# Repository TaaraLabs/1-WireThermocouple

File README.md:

1-Wire Thermocouple
==============

[WebSite](https://taaralabs.eu/tc1)

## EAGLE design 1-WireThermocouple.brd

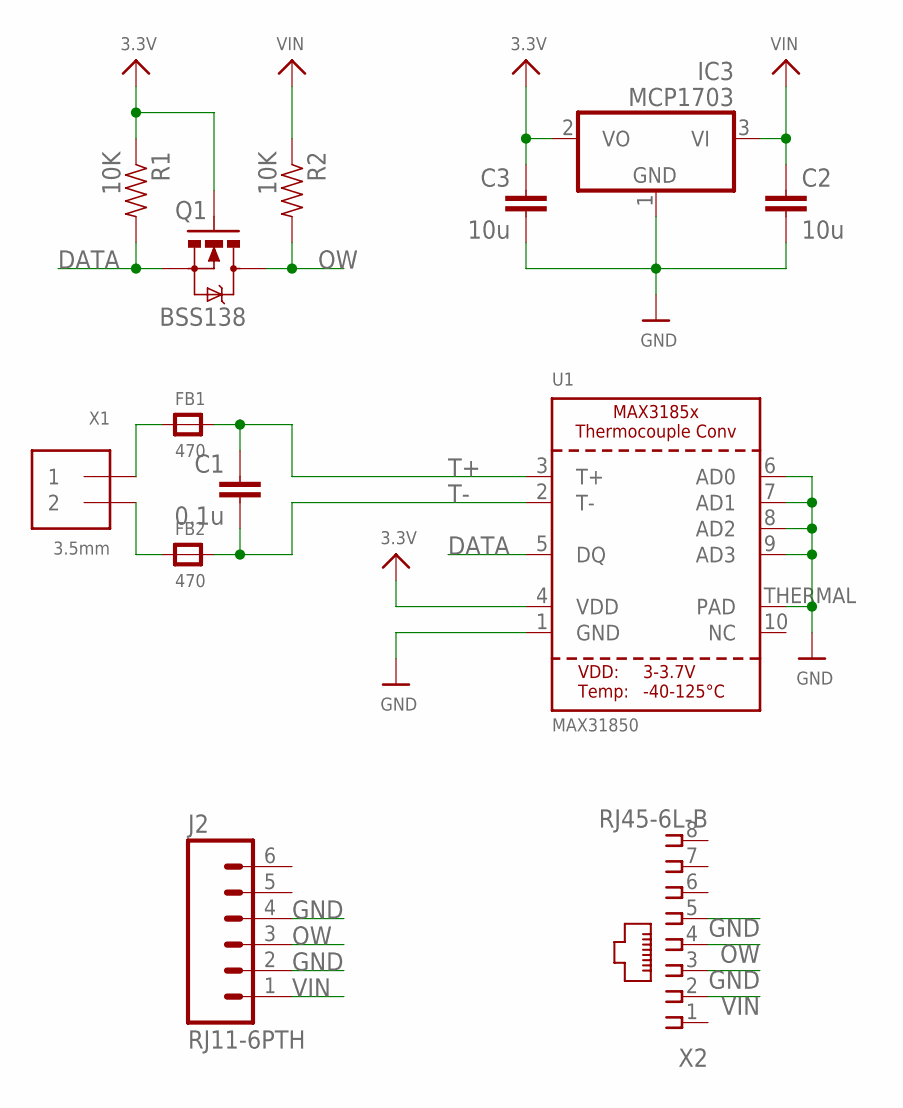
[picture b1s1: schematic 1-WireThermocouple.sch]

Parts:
C1: 0.1u; 0603-CAP
C2, C3: 10u; 0603-CAP
FB1, FB2: 470; 0603
IC3: MCP1703; SOT23
J2: RJ11-6PTH; RJ11-6
Q1: BSS138; SOT23-3
R1, R2: 10K; 0603-RES
U1: MAX31850; TDFN10_3X4MM
X1: 3.5mm; TERMBLOCK_1X2-3.5MM
X2: RJ45-6L-B; RJ45-NO-SHIELD

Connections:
3.3V: C3.1, IC3.2 (VO), Q1.1 (G), R1.1, U1.4 (VDD)
DATA: Q1.2 (S), R1.2, U1.5 (DQ)
GND: C2.2, C3.2, IC3.1 (GND), J2.2, J2.4, U1.1 (GND), U1.6 (AD0), U1.7 (AD1), U1.8 (AD2), U1.9 (AD3), U1.THERMAL (PAD), X2.3, X2.5
unnamed: FB1.1, X1.1
unnamed: FB2.1, X1.2
OW: J2.3, Q1.3 (D), R2.2, X2.4
T+: C1.1, FB1.2, U1.3 (T+)
T-: C1.2, FB2.2, U1.2 (T-)
VIN: C2.1, IC3.3 (VI), J2.1, R2.1, X2.2

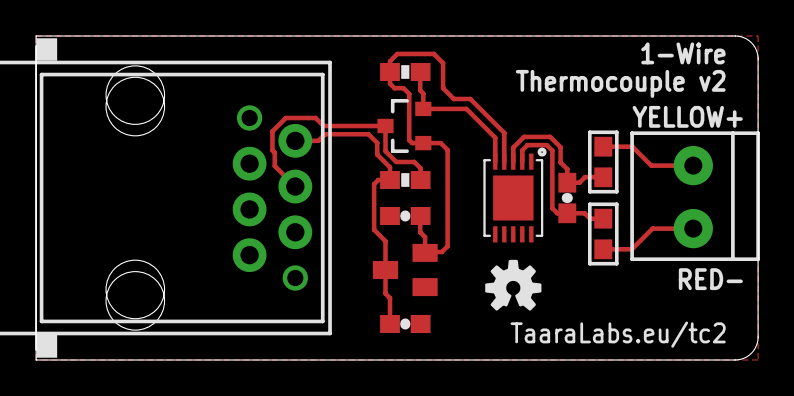
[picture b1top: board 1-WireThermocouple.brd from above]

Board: 2 copper layers, 40.1 x 18.0 mm, 15 parts (1 on the bottom side), 9 nets.

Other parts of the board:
U$1: OSHW-LOGO-S
U$8: OSHW-LOGO-L

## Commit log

2015-01-22 :octocat: Added .gitattributes & .gitignore files
2015-01-22 1-Wire Thermocouple
2019-04-16 LDO footprint fixed
2019-04-16 new images

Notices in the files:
parts and their libraries:
microbuilder: This work is placed in the public domain, and may be freely used for commercial and non-commercial work with the following conditions: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
SparkFun: Licensing: CC v3.0 Share-Alike You are welcome to use this library for commercial purposes.
